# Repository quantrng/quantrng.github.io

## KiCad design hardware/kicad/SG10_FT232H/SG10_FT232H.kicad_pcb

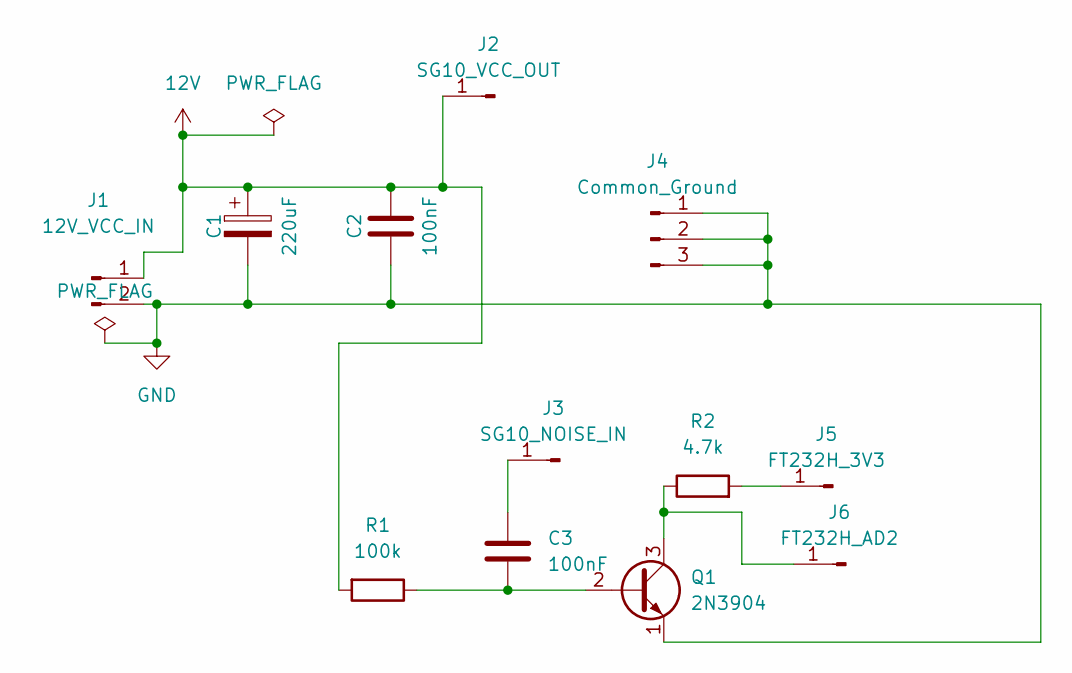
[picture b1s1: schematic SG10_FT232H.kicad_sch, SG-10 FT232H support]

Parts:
C1: 220uF; CP_Radial_D6.3mm_P2.50mm
C2, C3: 100nF; C_Disc_D5.0mm_W2.5mm_P2.50mm
J1: 12V_VCC_IN; PinHeader_1x02_P2.54mm_Vertical
J2: SG10_VCC_OUT; PinHeader_1x01_P2.54mm_Vertical
J3: SG10_NOISE_IN; PinHeader_1x01_P2.54mm_Vertical
J4: Common_Ground; PinHeader_1x03_P2.54mm_Vertical
J5: FT232H_3V3; PinHeader_1x01_P2.54mm_Vertical
J6: FT232H_AD2; PinHeader_1x01_P2.54mm_Vertical
Q1: 2N3904; TO-92_Inline
R1: 100k; R_Axial_DIN0207_L6.3mm_D2.5mm_P10.16mm_Horizontal
R2: 4.7k; R_Axial_DIN0207_L6.3mm_D2.5mm_P10.16mm_Horizontal

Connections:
12V: C1.1, C2.1, J1.1, J2.1 (Pin_1_1), R1.2
GND: C1.2, C2.2, J1.2, J4.1, J4.2, J4.3, Q1.1 (E)
unnamed: C3.1, J3.1 (Pin_1_1)
unnamed: J5.1 (Pin_1_1), R2.2
unnamed: J6.1 (Pin_1_1), Q1.3 (C), R2.1
unnamed: C3.2, Q1.2 (B), R1.1

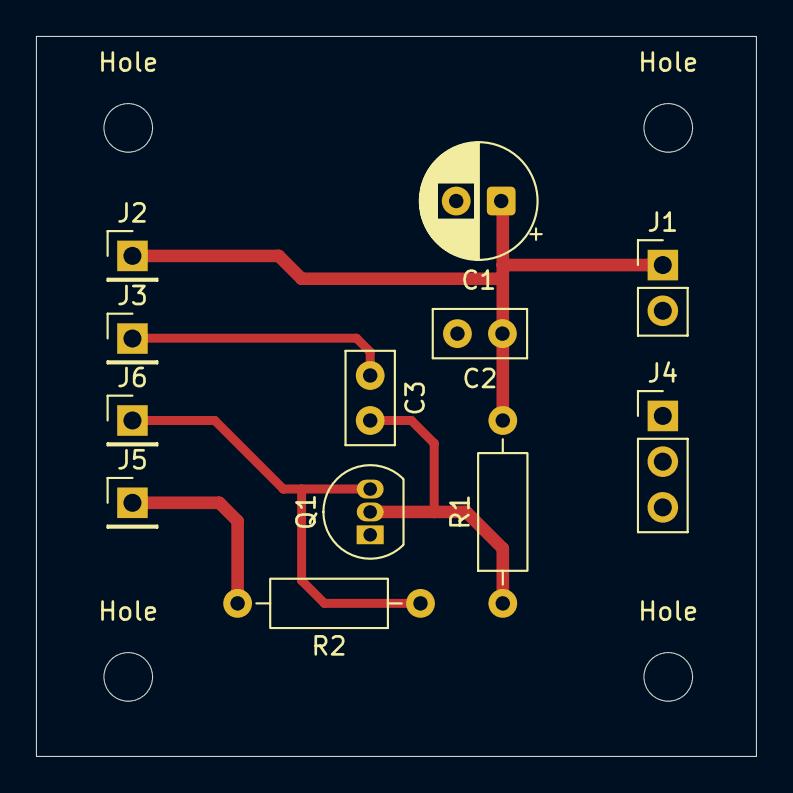
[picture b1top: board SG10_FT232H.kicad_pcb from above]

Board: 2 copper layers, 40.0 x 40.0 mm, 16 parts (0 on the bottom side), 6 nets.

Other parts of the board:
Hole: MountingHole_2.7mm_M2.5
Hole#2, Hole#3, Hole#4: MountingHole_2.7mm_M2.5
